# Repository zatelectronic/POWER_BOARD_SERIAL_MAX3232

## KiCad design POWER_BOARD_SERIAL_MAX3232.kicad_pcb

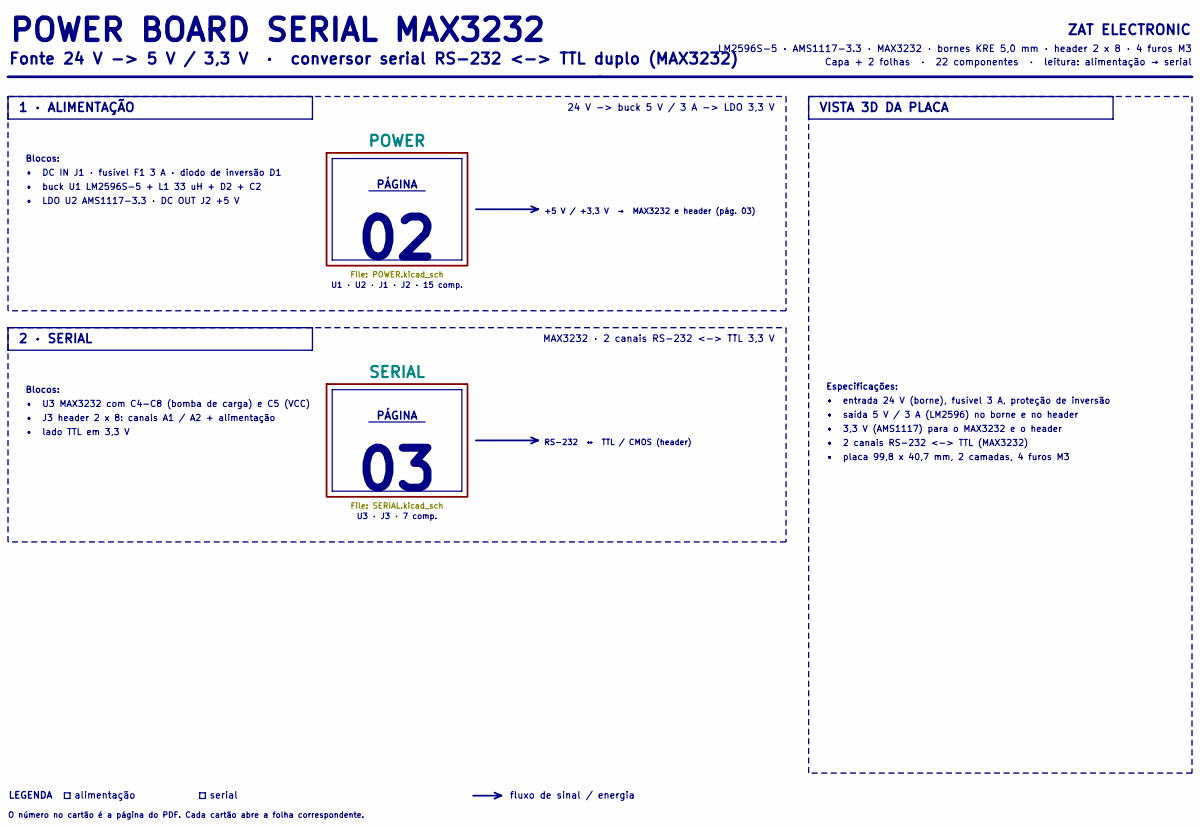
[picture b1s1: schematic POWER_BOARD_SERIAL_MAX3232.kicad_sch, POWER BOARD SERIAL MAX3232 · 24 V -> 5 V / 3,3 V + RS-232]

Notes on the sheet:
Blocos:
• buck U1 LM2596S-5 + L1 33 uH + D2 + C2
ZAT ELECTRONIC
POWER BOARD SERIAL MAX3232
• J3 header 2 x 8: canais A1 / A2 + alimentação
• lado TTL em 3,3 V
O número no cartão é a página do PDF. Cada cartão abre a folha correspondente.
U3 · J3 · 7 comp.
serial
• entrada 24 V (borne), fusível 3 A, proteção de inversão
fluxo de sinal / energia
1 · ALIMENTAÇÃO
LM2596S-5 · AMS1117-3.3 · MAX3232 · bornes KRE 5,0 mm · header 2 x 8 · 4 furos M3
MAX3232 · 2 canais RS-232 <-> TTL 3,3 V
RS-232 ↔ TTL / CMOS (header)
2 · SERIAL
Especificações:
• saída 5 V / 3 A (LM2596) no borne e no header
PÁGINA
• 3,3 V (AMS1117) para o MAX3232 e o header
• U3 MAX3232 com C4-C8 (bomba de carga) e C5 (VCC)
VISTA 3D DA PLACA
+5 V / +3,3 V → MAX3232 e header (pág. 03)
24 V -> buck 5 V / 3 A -> LDO 3,3 V
• placa 99,8 x 40,7 mm, 2 camadas, 4 furos M3
Fonte 24 V -> 5 V / 3,3 V · conversor serial RS-232 <-> TTL duplo (MAX3232)
Capa + 2 folhas · 22 componentes · leitura: alimentação → serial
• DC IN J1 · fusível F1 3 A · diodo de inversão D1
U1 · U2 · J1 · J2 · 15 comp.
• LDO U2 AMS1117-3.3 · DC OUT J2 +5 V
• 2 canais RS-232 <-> TTL (MAX3232)
alimentação
LEGENDA

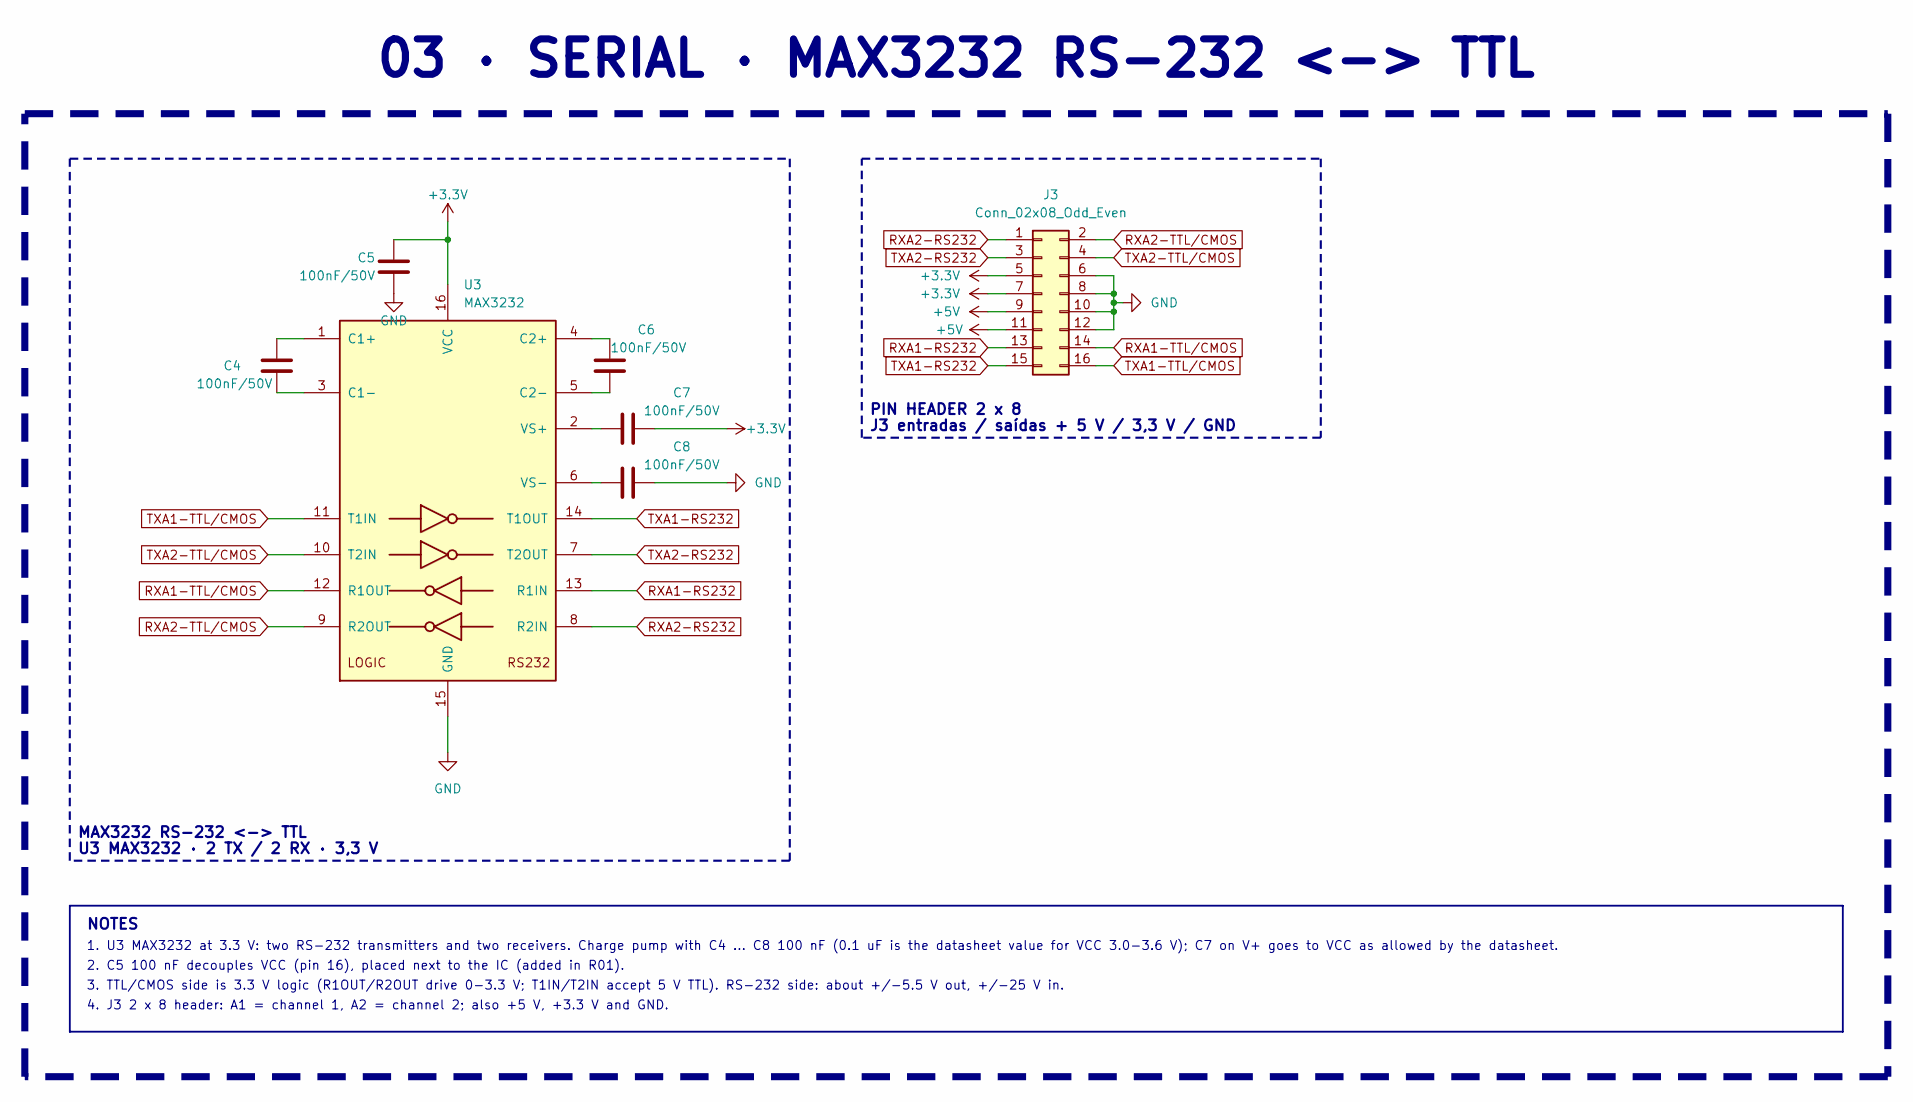
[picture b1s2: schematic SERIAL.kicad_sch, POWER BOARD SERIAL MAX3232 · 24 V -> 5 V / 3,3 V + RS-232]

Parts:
C4, C5, C6, C7, C8: 100nF/50V; C_0805_2012Metric
J3: Conn_02x08_Odd_Even; PinHeader_2x08_P2.54mm_Vertical
U3: MAX3232; SOIC-16_3.9x9.9mm_P1.27mm

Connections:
+3.3V: C5.1, C7.2, J3.5, J3.7, U3.16 (VCC); also elsewhere on the board
+5V: J3.9, J3.11; also elsewhere on the board
GND: C5.2, C8.2, J3.6, J3.8, J3.10, J3.12, U3.15 (GND); also elsewhere on the board
unnamed: C4.1, U3.1 (C1+)
unnamed: C4.2, U3.3 (C1-)
unnamed: C6.1, U3.4 (C2+)
unnamed: C6.2, U3.5 (C2-)
unnamed: C7.1, U3.2 (VS+)
unnamed: C8.1, U3.6 (VS-)
RXA1-RS232: J3.13, U3.13 (R1IN)
RXA1-TTL/CMOS: J3.14, U3.12 (R1OUT)
RXA2-RS232: J3.1, U3.8 (R2IN)
RXA2-TTL/CMOS: J3.2, U3.9 (R2OUT)
TXA1-RS232: J3.15, U3.14 (T1OUT)
TXA1-TTL/CMOS: J3.16, U3.11 (T1IN)
TXA2-RS232: J3.3, U3.7 (T2OUT)
TXA2-TTL/CMOS: J3.4, U3.10 (T2IN)

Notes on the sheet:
2. C5 100 nF decouples VCC (pin 16), placed next to the IC (added in R01).
4. J3 2 x 8 header: A1 = channel 1, A2 = channel 2; also +5 V, +3.3 V and GND.
MAX3232 RS-232 <-> TTL
J3 entradas / saídas + 5 V / 3,3 V / GND
3. TTL/CMOS side is 3.3 V logic (R1OUT/R2OUT drive 0-3.3 V; T1IN/T2IN accept 5 V TTL). RS-232 side: about +/-5.5 V out, +/-25 V in.
PIN HEADER 2 x 8
1. U3 MAX3232 at 3.3 V: two RS-232 transmitters and two receivers. Charge pump with C4 ... C8 100 nF (0.1 uF is the datasheet value for VCC 3.0-3.6 V); C7 on V+ goes to VCC as allowed by the datasheet.
U3 MAX3232 · 2 TX / 2 RX · 3,3 V
03 · SERIAL · MAX3232 RS-232 <-> TTL
NOTES

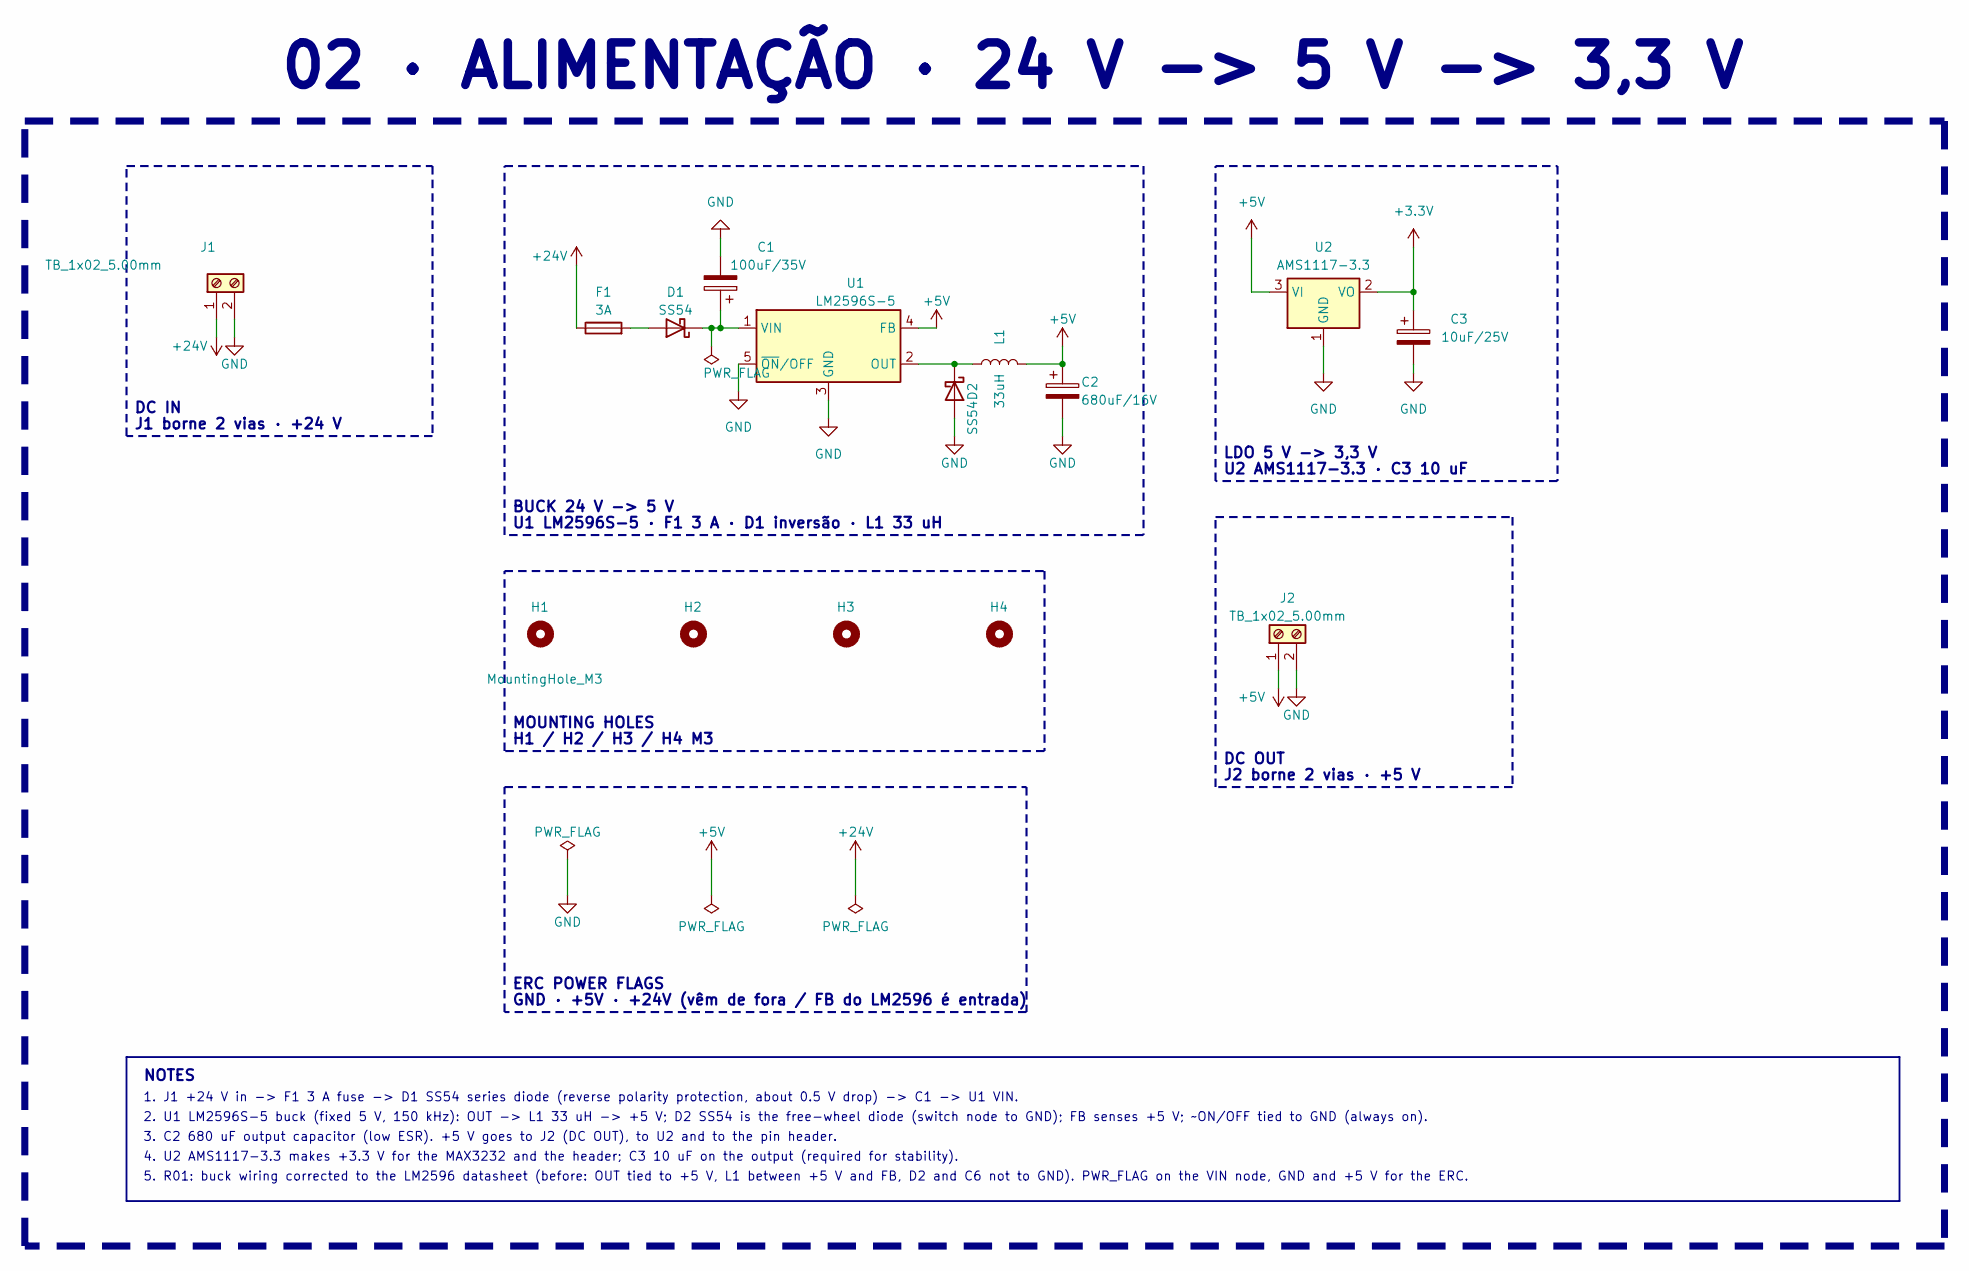
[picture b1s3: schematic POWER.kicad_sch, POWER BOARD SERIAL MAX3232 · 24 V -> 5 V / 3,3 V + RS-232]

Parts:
C1: 100uF/35V; CP_Elec_10x10
C2: 680uF/16V; CP_Elec_10x12.5
C3: 10uF/25V; CP_Elec_4x5.4
D1, D2: SS54; D_SMA
F1: 3A; Fuse_2010_5025Metric_Pad1.52x2.65mm_HandSolder_1808-2410
H1, H2, H3, H4: MountingHole_M3; MountingHole_3.2mm_M3_ISO14580
J1, J2: TB_1x02_5.00mm; TerminalBlock_MaiXu_MX126-5.0-02P_1x02_P5.00mm_DG306
L1: 33uH; L_12x12mm_H8mm_33uH
U1: LM2596S-5; TO-263-5_TabPin3
U2: AMS1117-3.3; SOT-223-3_TabPin2

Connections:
+3.3V: C3.1, U2.2 (VO); also elsewhere on the board
+5V: C2.1, J2.1, L1.1, U1.4 (FB), U2.3 (VI); also elsewhere on the board
+24V: F1.1, J1.1
GND: C1.2, C2.2, C3.2, D2.2 (A), J1.2, J2.2, U1.3 (GND), U1.5 (~ON/OFF), U2.1 (GND); also elsewhere on the board
unnamed: D1.2 (A), F1.2
unnamed: C1.1, D1.1 (K), U1.1 (VIN)
unnamed: D2.1 (K), L1.2, U1.2 (OUT)

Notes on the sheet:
5. R01: buck wiring corrected to the LM2596 datasheet (before: OUT tied to +5 V, L1 between +5 V and FB, D2 and C6 not to GND). PWR_FLAG on the VIN node, GND and +5 V for the ERC.
DC OUT
H1 / H2 / H3 / H4 M3
J2 borne 2 vias · +5 V
DC IN
GND · +5V · +24V (vêm de fora / FB do LM2596 é entrada)
2. U1 LM2596S-5 buck (fixed 5 V, 150 kHz): OUT -> L1 33 uH -> +5 V; D2 SS54 is the free-wheel diode (switch node to GND); FB senses +5 V; ~ON/OFF tied to GND (always on).
1. J1 +24 V in -> F1 3 A fuse -> D1 SS54 series diode (reverse polarity protection, about 0.5 V drop) -> C1 -> U1 VIN.
NOTES
LDO 5 V -> 3,3 V
3. C2 680 uF output capacitor (low ESR). +5 V goes to J2 (DC OUT), to U2 and to the pin header.
BUCK 24 V -> 5 V
02 · ALIMENTAÇÃO · 24 V -> 5 V -> 3,3 V
U1 LM2596S-5 · F1 3 A · D1 inversão · L1 33 uH
U2 AMS1117-3.3 · C3 10 uF
J1 borne 2 vias · +24 V
MOUNTING HOLES
4. U2 AMS1117-3.3 makes +3.3 V for the MAX3232 and the header; C3 10 uF on the output (required for stability).
ERC POWER FLAGS

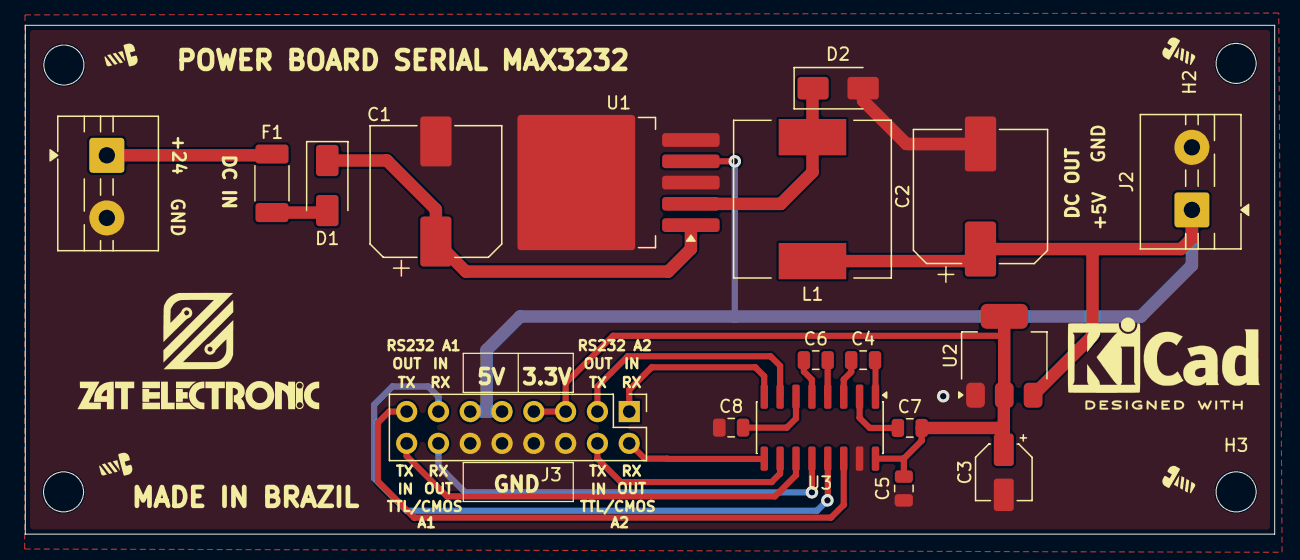
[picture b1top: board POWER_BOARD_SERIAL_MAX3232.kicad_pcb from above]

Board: 2 copper layers, 99.8 x 40.6 mm, 22 parts (0 on the bottom side), 21 nets.
